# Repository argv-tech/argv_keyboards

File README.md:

# ARGV Keyboards

Keyboard Layout Editor definitions and printable keycap models for building and experimenting with custom keyboards.

The repository contains two keyboard layouts plus four ScottoCaps profiles. Ready-to-print meshes, editable CAD files, and original Shapr3D sources are included where available.

## Quick start

Choose a layout:

- [`keyboard-layout.json`](keyboard-layout.json) — split 80-key layout.
- [`keyboard-layout-no-split.json`](keyboard-layout-no-split.json) — non-split 106-key layout.

Then:

1. To view or edit the layout, open [Keyboard Layout Editor](https://www.keyboard-layout-editor.com/), select **Raw data**, and paste in the contents of the JSON file.
2. Choose a keycap profile and confirm that it supports your switch type and printing process.
3. Open a `.3mf` or `.stl` file in your slicer. Use the matching `.step` or `.shapr` file if you need to modify the geometry.
4. Print a single `1.00u` keycap first and test the stem fit before printing a full set.

## Keycap profiles

| Profile | Switches | Process | Contents | Documentation |
| --- | --- | --- | --- | --- |
| Flat | Cherry MX | FDM | Low-profile blanks and legends | [Printing notes](ScottoCaps/Flat/Readme.md) |
| Glass | Cherry MX and Choc | MSLA resin | Low-profile blanks from 1.00u to 10.00u, depending on switch type | [Safety and printing notes](ScottoCaps/Glass/README.md) |
| Scooped | Cherry MX and Choc | FDM | Concave, convex, homing, and multi-size caps; extensive legend collection | [Dimensions and printing notes](ScottoCaps/Scooped/Readme.md) |
| Sculpted | Cherry MX | FDM | R1–R5 blank keycaps in multiple sizes | [Dimensions and printing notes](ScottoCaps/Sculpted/Readme.md) |

### File formats

| Extension | Use |
| --- | --- |
| `.3mf` | Preferred slicer-ready model, including legend objects where applicable |
| `.stl` | Widely supported printable mesh |
| `.step` | Editable solid model for CAD applications |
| `.shapr` | Original Shapr3D project |
| `.json` | Keyboard Layout Editor raw data |

## Printing notes

- **Check compatibility first.** MX and Choc stems are different; use the directory for your switch type.
- **Test the stem fit.** The FDM stems use an approximately 0.15 mm tolerance, so the result depends on printer calibration and material. Never force a tight cap onto a switch.
- **Use dual extrusion for legends.** The Scooped legend variants are designed for a dual-extruder or multi-material printer.
- **Use biocompatible resin for Glass caps.** These caps are handled continuously and must be printed with an appropriate biocompatible resin. Read the [Glass safety notes](ScottoCaps/Glass/README.md) before printing.
- **Expect to tune the model or slicer.** Stem fit, rotation, and surface finish vary between printers. Each profile's documentation contains its recommended orientation and adjustments.

## Repository structure

```text
.
├── keyboard-layout.json
├── keyboard-layout-no-split.json
└── ScottoCaps/
    ├── Flat/
    │   ├── Blanks/
    │   └── Legends/
    ├── Glass/
    │   ├── Choc/
    │   └── MX/
    ├── Scooped/
    │   ├── Choc/
    │   └── MX/
    └── Sculpted/
        └── Blanks/
```

File names encode the key width in keyboard units (`u`). Scooped Choc models also include their physical footprint (`16x16`, `18x17`, or `18x18`), while Sculpted files include the row (`R1`–`R5`).

## Contributing

When adding or changing an asset:

- Keep the existing profile, switch, size, and variant naming conventions.
- Include an editable `.step` model alongside printable meshes when possible.
- Update the relevant profile README with any new dimensions, materials, or slicer requirements.
- Confirm that edited layout files still load in Keyboard Layout Editor.

## Credits

Special thanks to [ScottoKeebs](https://scottokeebs.com/) for the keycap models and printing guidance. The original designs and source files are available in the [ScottoKeebs GitHub repository](https://github.com/joe-scotto/scottokeebs/).

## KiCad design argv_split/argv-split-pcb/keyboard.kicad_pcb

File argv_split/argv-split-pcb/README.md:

# Split keyboard — one fabrication file, two cable-connected halves

Open `keyboard.kicad_pro` in KiCad 10. The PCB is one fabrication file containing two separately cuttable halves, so both halves can be sent in one order. U1 is the left Pico and U2 is the right Pico. Existing switch positions are preserved. Use standard, non-wireless Raspberry Pi Pico 1 modules with two 20-pin, 2.54 mm headers/sockets. USB connectors face the top edge. The modules supply their own regulation and USB circuitry.

All routed copper segments are 0.4 mm. The top and left edges were moved to leave at least 5 mm between the board edge and the switch courtyard; the other edges already meet that margin. The two halves have no PCB copper link: the four-wire cable is the only connection between them.

The project rules use a JLCPCB-friendly 2-layer baseline: 0.2 mm copper clearance, 0.4 mm minimum track width, 0.6/0.3 mm vias, 0.15 mm minimum via annular width, 0.09 mm soldermask expansion clearance, and 1.0 mm / 0.15 mm silkscreen text height and stroke. The 0.2 mm clearance is deliberately stricter than JLCPCB's published 0.10 mm capability so the board has process margin. See [JLCPCB's PCB capabilities](https://jlcpcb.com/capabilities/pcb-capabilities). Run the final DRC and JLCDFM check on the exported Gerbers before ordering.

The widened 0.4 mm tracks are applied to the existing compact routing. With the stricter 0.2 mm clearance rule, the current DRC report flags 75 clearance violations. Treat this revision as a routing review checkpoint and do not order until those routes are respaced or the JLCPCB DFM result confirms the actual geometry.

**Connector fit is not yet confirmed.** J1/J2 are standard 1×4, 2.54 mm through-hole headers for wiring to a separate connector PCB. They are not a verified footprint for the purchased four-pin part. Confirm its model, pitch, pin order, mounting, and cable continuity before fabrication. The board outlines are proposed outlines; check them against the intended plate/case.

## Four-wire interconnect

Use 3.3 V logic, full-duplex UART. GP0 is TX and GP1 is RX on both Picos. The right connector swaps the signal assignments, so a pin-for-pin cable crosses TX to RX:

| Cable pin | J1 / left | J2 / right |
| --- | --- | --- |
| 1 | U1 pin 39, VSYS | U2 pin 39, VSYS |
| 2 | Ground | Ground |
| 3 | U1 pin 1, GP0 / TX | U2 pin 2, GP1 / RX |
| 4 | U1 pin 2, GP1 / RX | U2 pin 1, GP0 / TX |

Cable connections: 1–1, 2–2, 3–3, 4–4. Do not add a second TX/RX crossover in the cable. Connect USB to one Pico; its onboard VBUS-to-VSYS Schottky diode supplies both halves through the VSYS wire. Do not connect the Pico 3V3 regulator outputs together. The schematic uses separate left/right net names because the cable is external, not a copper trace between boards.

Connect or disconnect the interconnect with USB power removed, especially if the purchased connector is TRRS: its contacts can short during insertion. This interface is not designed for live insertion.

## Matrix mapping

Diode cathodes connect to rows: firmware diode direction is `COL2ROW`. Each half has a logical 5×8 matrix with unused positions. GPIO names below refer to RP2040 GPIO numbers, not physical Pico pin numbers.

| GPIO | Pico pin | Left net | Right net |
| --- | --- | --- | --- |
| GP2 | 4 | ROW0 | ROW8 |
| GP3 | 5 | ROW1 | ROW7 |
| GP4 | 6 | ROW2 | ROW6 |
| GP5 | 7 | ROW3 | ROW5 |
| GP6 | 9 | ROW9 | ROW4 |
| GP7 | 10 | COL0 | COL8 |
| GP8 | 11 | COL1 | COL9 |
| GP9 | 12 | COL2 | COL10 |
| GP10 | 14 | COL3 | COL11 |
| GP11 | 15 | COL4 | COL12 |
| GP12 | 16 | COL5 | COL13 |
| GP13 | 17 | COL6 | COL14 |
| GP14 | 19 | COL7 | COL15 |

For split firmware, the global schematic ROW/COL numbers need translating to each half's local five rows and eight columns using this table. Firmware is not included or tested in this hardware project.

## Cable transport

Only the Pico-to-connector traces are on the PCBs. The inter-half TX/RX connection runs through the cable, and the cable can be rewired when a board is used on the opposite side. The right-hand connector swaps pins 3 and 4 so a straight pin-for-pin cable works with the two halves.

The UART baud rate is programmable; start at a conservative rate and verify the actual cable and firmware before increasing it. Scan rate, debounce and USB scheduling also affect keyboard latency.

QMK supports RP2040 full-duplex serial transport. Follow its driver configuration for GP0/GP1 and the selected driver; a complete keymap and handedness configuration are still required.

Sources: [RP2040 datasheet, UART §4.2 and I²C §4.3](https://datasheets.raspberrypi.com/rp2040/rp2040-datasheet.pdf), [QMK serial drivers](https://docs.qmk.fm/drivers/serial), [QMK RP2040 support](https://docs.qmk.fm/platformdev_rp2040), [Pico board datasheet](https://datasheets.raspberrypi.com/pico/pico-datasheet.pdf).

## Verification and previews

- `reports/erc.json`: schematic electrical checks.
- `reports/drc.json`: PCB design rules, unconnected items, and schematic parity.
- `reports/pcb-preview.png`: latest saved PCB preview.
- `reports/schematic/keyboard.svg`: schematic preview.
- `scripts/validate_design.py`: independent checks of connector and matrix pin mapping, and trace confinement to the two outlines.

If an already-open PCB editor shows long traces across the gap or below the boards, close that older in-memory view without saving and reopen the current project from disk. Avoid overwriting the updated file with the older view.

The scripts used for one-time construction are retained for traceability. Do not rerun `add_controllers.py`, `finish_connections.py`, `sync_board.py`, `finish_presentation.py`, or `clarify_schematic.py` on the finished design: some are one-time migrations and `sync_board.py` intentionally removes routing before autorouting. Edit the KiCad files normally for subsequent changes.

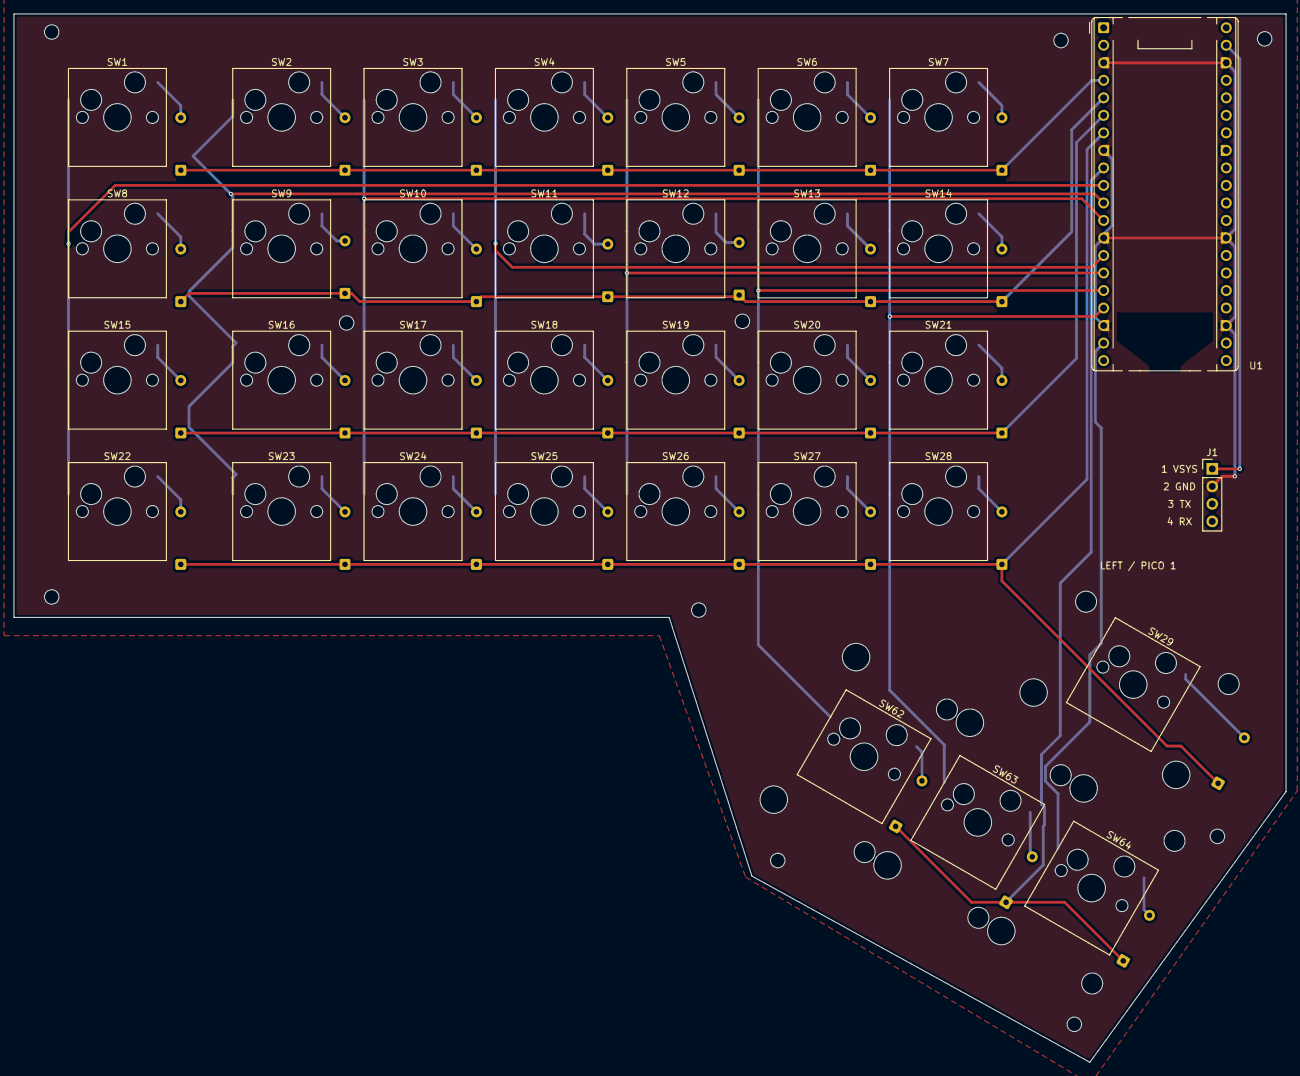
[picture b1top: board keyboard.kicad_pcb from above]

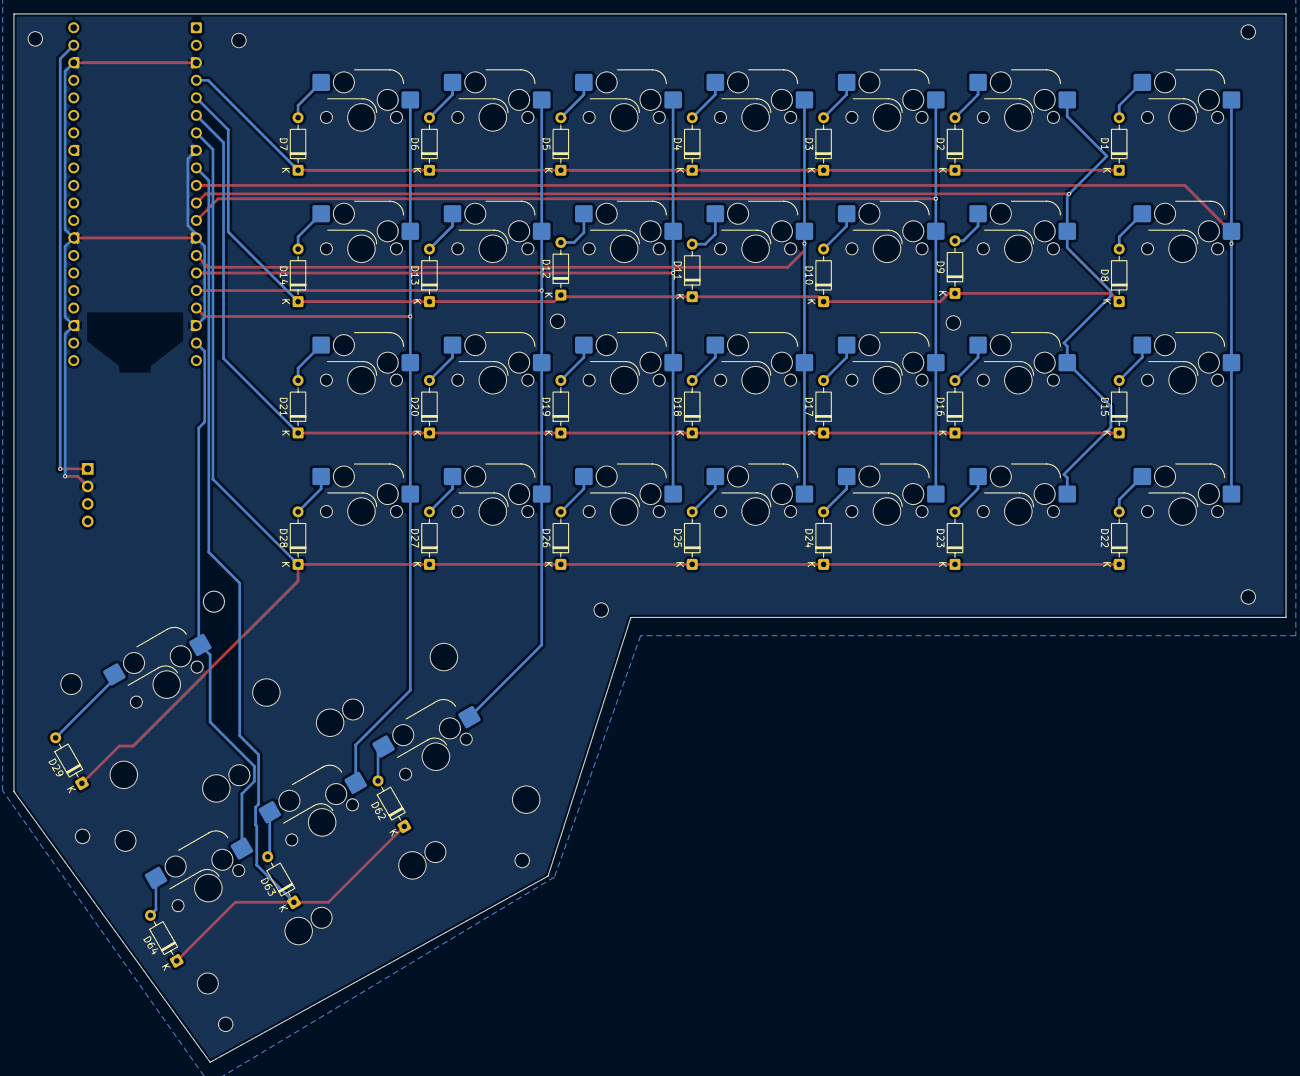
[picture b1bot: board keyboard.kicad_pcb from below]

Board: 2 copper layers, 184.4 x 152.0 mm, 80 parts (32 on the bottom side), 49 nets.

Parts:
D1, D2, D3, D4, D5, D6, D7, D8, D9, D10, D11, D12, D13, D14, D15, D16, D17, D18, D19, D20, D21, D22, D23, D24, D25, D26, D27, D28, D29, D62, D63, D64: D; D_DO-35_SOD27_P7.62mm_Horizontal
H1, H2, H3, H4, H5, H6, H7, H7#2, H7#3, H8: MountingHole_2.1mm
J1: BREAKOUT_4PIN; PinHeader_1x04_P2.54mm_Vertical
ST29, ST62, ST63, ST64: SW_stab; Stabilizer_Cherry_MX_2.00u
SW1, SW8, SW15, SW22: SW_Push; SW_Hotswap_Kailh_MX_1.50u
SW2, SW3, SW4, SW5, SW6, SW7, SW9, SW10, SW11, SW12, SW13, SW14, SW16, SW17, SW18, SW19, SW20, SW21, SW23, SW24, SW25, SW26, SW27, SW28, SW62, SW63, SW64: SW_Push; SW_Hotswap_Kailh_MX_1.00u
SW29: SW_Push; SW_Hotswap_Kailh_MX_2.00u
U1: RaspberryPi_Pico; RaspberryPi_Pico_Case_THT

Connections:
COL0: SW1.1, SW8.1, SW15.1, SW22.1, U1.10 (GPIO7)
COL1: SW2.1, SW9.1, SW16.1, SW23.1, U1.11 (GPIO8)
COL2: SW3.1, SW10.1, SW17.1, SW24.1, U1.12 (GPIO9)
COL3: SW4.1, SW11.1, SW18.1, SW25.1, U1.14 (GPIO10)
COL4: SW5.1, SW12.1, SW19.1, SW26.1, U1.15 (GPIO11)
COL5: SW6.1, SW13.1, SW20.1, SW27.1, SW62.1, U1.16 (GPIO12)
COL6: SW7.1, SW14.1, SW21.1, SW28.1, SW63.1, U1.17 (GPIO13)
COL7: SW29.1, SW64.1, U1.19 (GPIO14)
L_GND: J1.2, U1.3 (GND), U1.8 (GND), U1.13 (GND), U1.18 (GND), U1.23 (GND), U1.28 (GND), U1.38 (GND)
L_RX: J1.4, U1.2 (GPIO1)
L_TX: J1.3, U1.1 (GPIO0)
L_VSYS: J1.1, U1.39 (VSYS)
unnamed: D1.2 (A), SW1.2
unnamed: D2.2 (A), SW2.2
unnamed: D3.2 (A), SW3.2
unnamed: D4.2 (A), SW4.2
unnamed: D5.2 (A), SW5.2
unnamed: D6.2 (A), SW6.2
unnamed: D7.2 (A), SW7.2
unnamed: D8.2 (A), SW8.2
unnamed: D9.2 (A), SW9.2
unnamed: D10.2 (A), SW10.2
unnamed: D11.2 (A), SW11.2
unnamed: D12.2 (A), SW12.2
unnamed: D13.2 (A), SW13.2
unnamed: D14.2 (A), SW14.2
unnamed: D15.2 (A), SW15.2
unnamed: D16.2 (A), SW16.2
unnamed: D17.2 (A), SW17.2
unnamed: D18.2 (A), SW18.2
unnamed: D19.2 (A), SW19.2
unnamed: D20.2 (A), SW20.2
unnamed: D21.2 (A), SW21.2
unnamed: D22.2 (A), SW22.2
unnamed: D23.2 (A), SW23.2
unnamed: D24.2 (A), SW24.2
unnamed: D25.2 (A), SW25.2
unnamed: D26.2 (A), SW26.2
unnamed: D27.2 (A), SW27.2
unnamed: D28.2 (A), SW28.2
unnamed: D29.2 (A), SW29.2
unnamed: D62.2 (A), SW62.2
unnamed: D63.2 (A), SW63.2
unnamed: D64.2 (A), SW64.2
ROW0: D1.1 (K), D2.1 (K), D3.1 (K), D4.1 (K), D5.1 (K), D6.1 (K), D7.1 (K), U1.4 (GPIO2)
ROW1: D8.1 (K), D9.1 (K), D10.1 (K), D11.1 (K), D12.1 (K), D13.1 (K), D14.1 (K), U1.5 (GPIO3)
ROW2: D15.1 (K), D16.1 (K), D17.1 (K), D18.1 (K), D19.1 (K), D20.1 (K), D21.1 (K), U1.6 (GPIO4)
ROW3: D22.1 (K), D23.1 (K), D24.1 (K), D25.1 (K), D26.1 (K), D27.1 (K), D28.1 (K), D29.1 (K), U1.7 (GPIO5)
ROW9: D62.1 (K), D63.1 (K), D64.1 (K), U1.9 (GPIO6)

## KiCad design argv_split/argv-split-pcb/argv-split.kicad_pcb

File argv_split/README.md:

# argv_split

`argv_split` is a custom split ergonomic keyboard based on the ErgoDox. It keeps
the familiar two-half layout and thumb clusters while adapting the electronics
and key arrangement for this project.

## Features

- Split ergonomic layout with separated left and right key groups
- 76 keys with dedicated thumb clusters
- Kailh hot-swap sockets for MX-compatible switches
- One diode per key for matrix isolation
- A Raspberry Pi Pico controller on each half
- Four-pin connectors for communication and power between the halves

## Project files

The design files are located in this directory:

- [`argv_split_kicad/argv_split_kicad.kicad_sch`](argv_split_kicad/argv_split_kicad.kicad_sch) — circuit schematic
- [`argv_split_kicad/argv_split_kicad.kicad_pcb`](argv_split_kicad/argv_split_kicad.kicad_pcb) — PCB layout
- [`argv_split_kicad/argv_split_kicad.kicad_pro`](argv_split_kicad/argv_split_kicad.kicad_pro) — KiCad project settings
- [`keyboard-layout.json`](keyboard-layout.json) — physical layout data for Keyboard Layout Editor
- [`keyboard_layout.dxf`](keyboard_layout.dxf) — exported layout geometry

Open `argv_split_kicad/argv_split_kicad.kicad_pro` in KiCad to inspect or
modify the design.

## Layout

The keyboard uses a 76-key split layout:

- 12 function keys (`F1`–`F12`), with six on each half
- 56 keys in four horizontal main rows, with seven keys per half in each row
- 8 thumb keys in two clusters rotated 30 degrees toward the center

The outer keys in the main block are 1.5u wide. The inner columns contain
parenthesis, brace, bracket, and quote keys. The left thumb cluster contains a
2u `Space` key above three 2u-tall keys labeled `Crtl`, `Linux`, and `Alt`. The
right cluster mirrors it with a 2u `backspace` key above `Return`, `Linux`, and
`Crtl`. These names and spellings match the current layout data.

To view or edit the layout, open Keyboard Layout Editor, choose **Raw data**, and
paste in the contents of [`keyboard-layout.json`](keyboard-layout.json). The
labels in this file describe the intended physical layout; the active key
behavior still depends on the keyboard firmware and keymap.

## Status

This is a custom hardware project and may still be a work in progress. Review
the schematic, PCB layout, footprints, clearances, and connector pinout before
ordering boards or assembling the keyboard.

## Attribution

This design is inspired by and derived from the ErgoDox keyboard layout, with
modifications made for the ARGV split keyboard project.

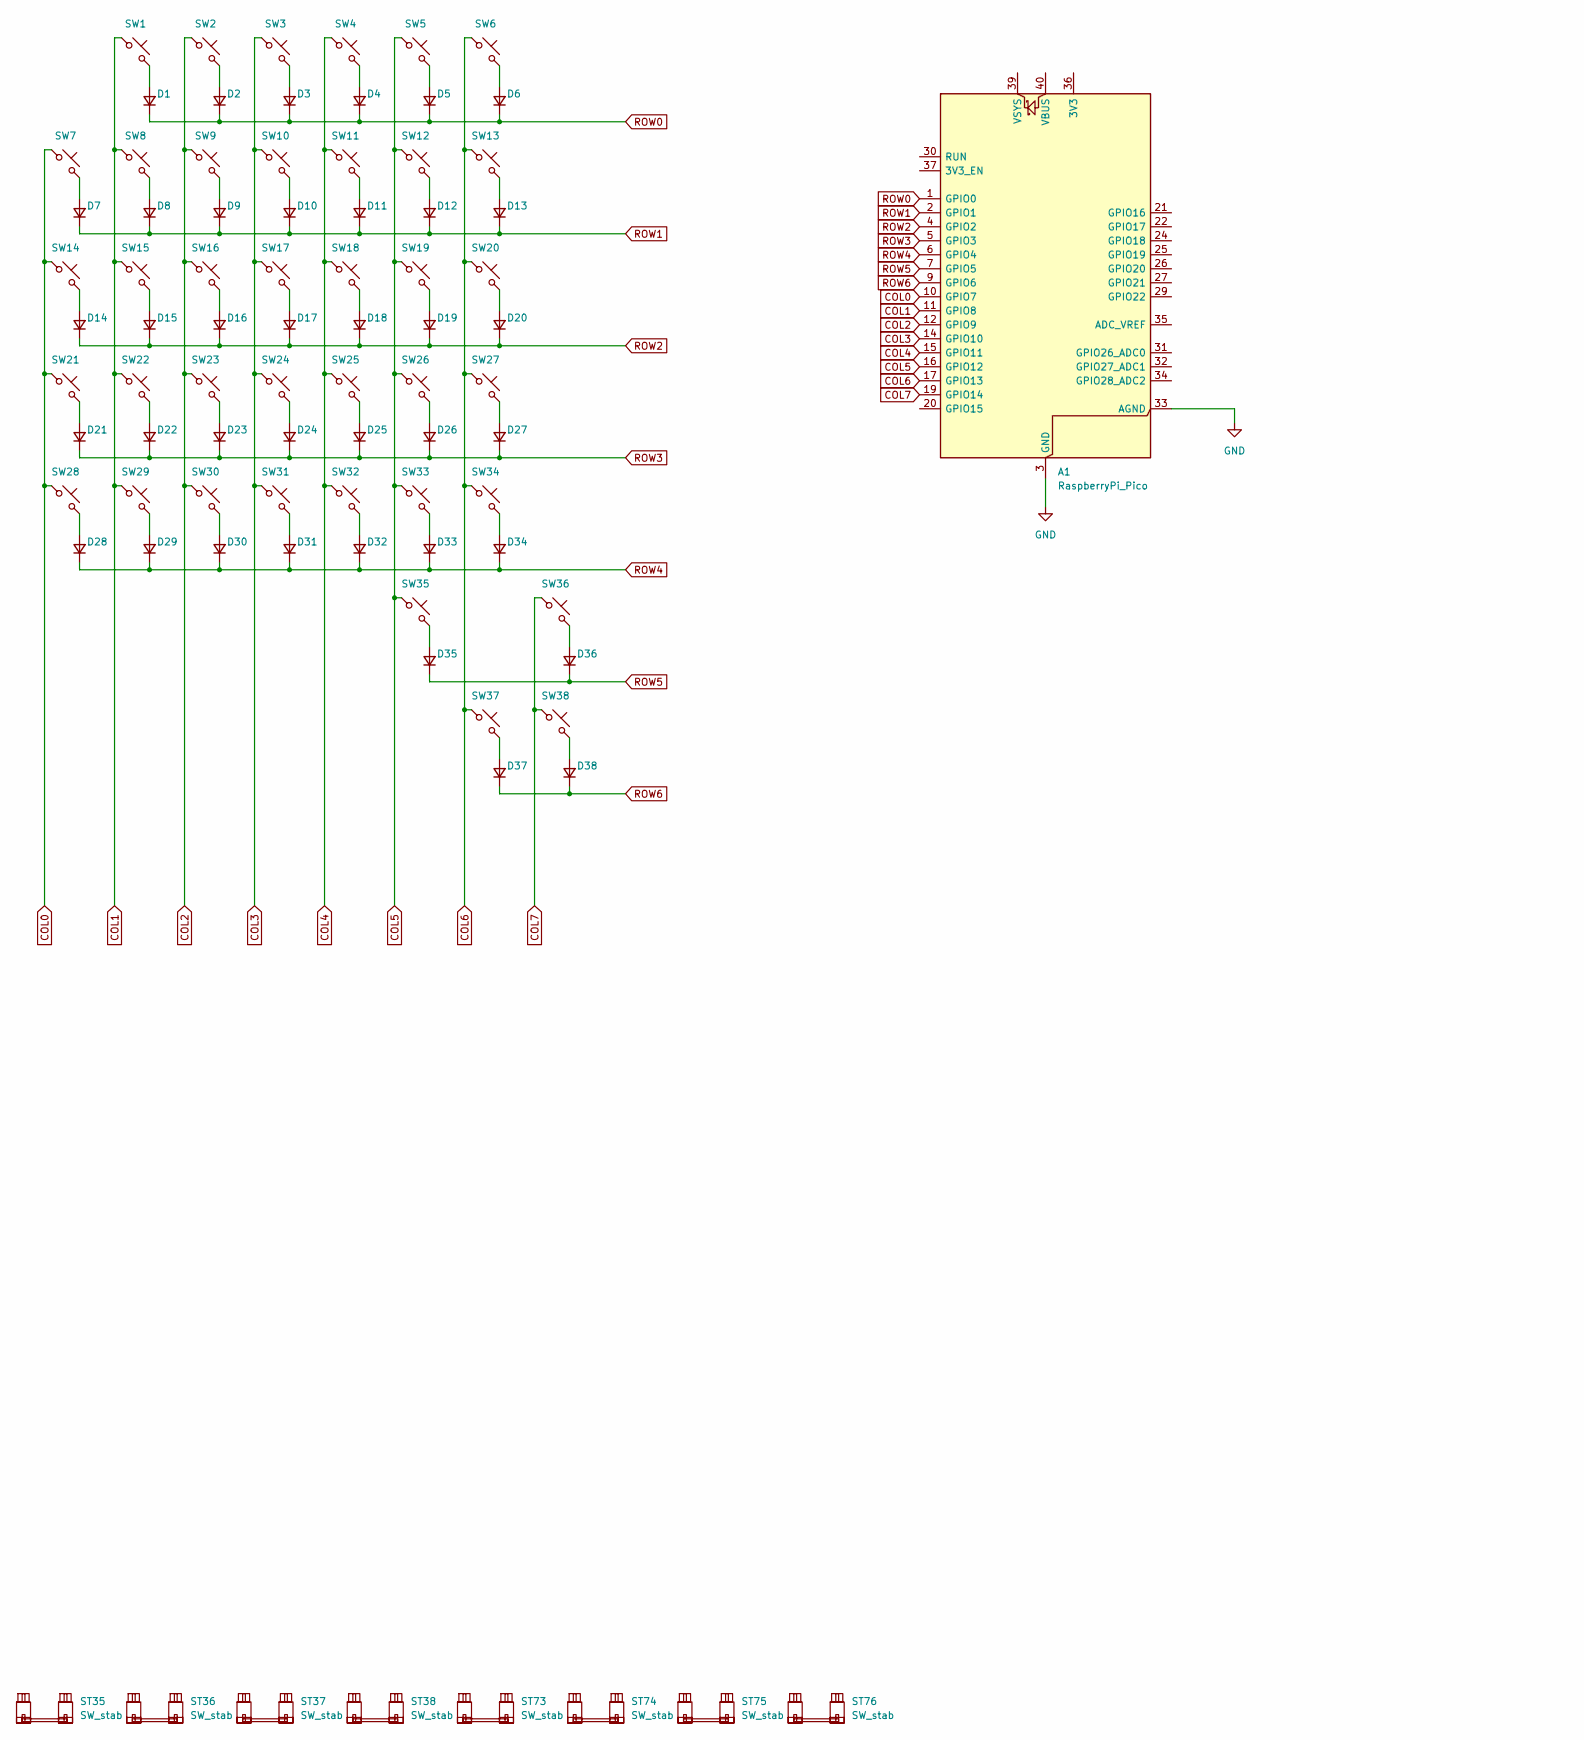
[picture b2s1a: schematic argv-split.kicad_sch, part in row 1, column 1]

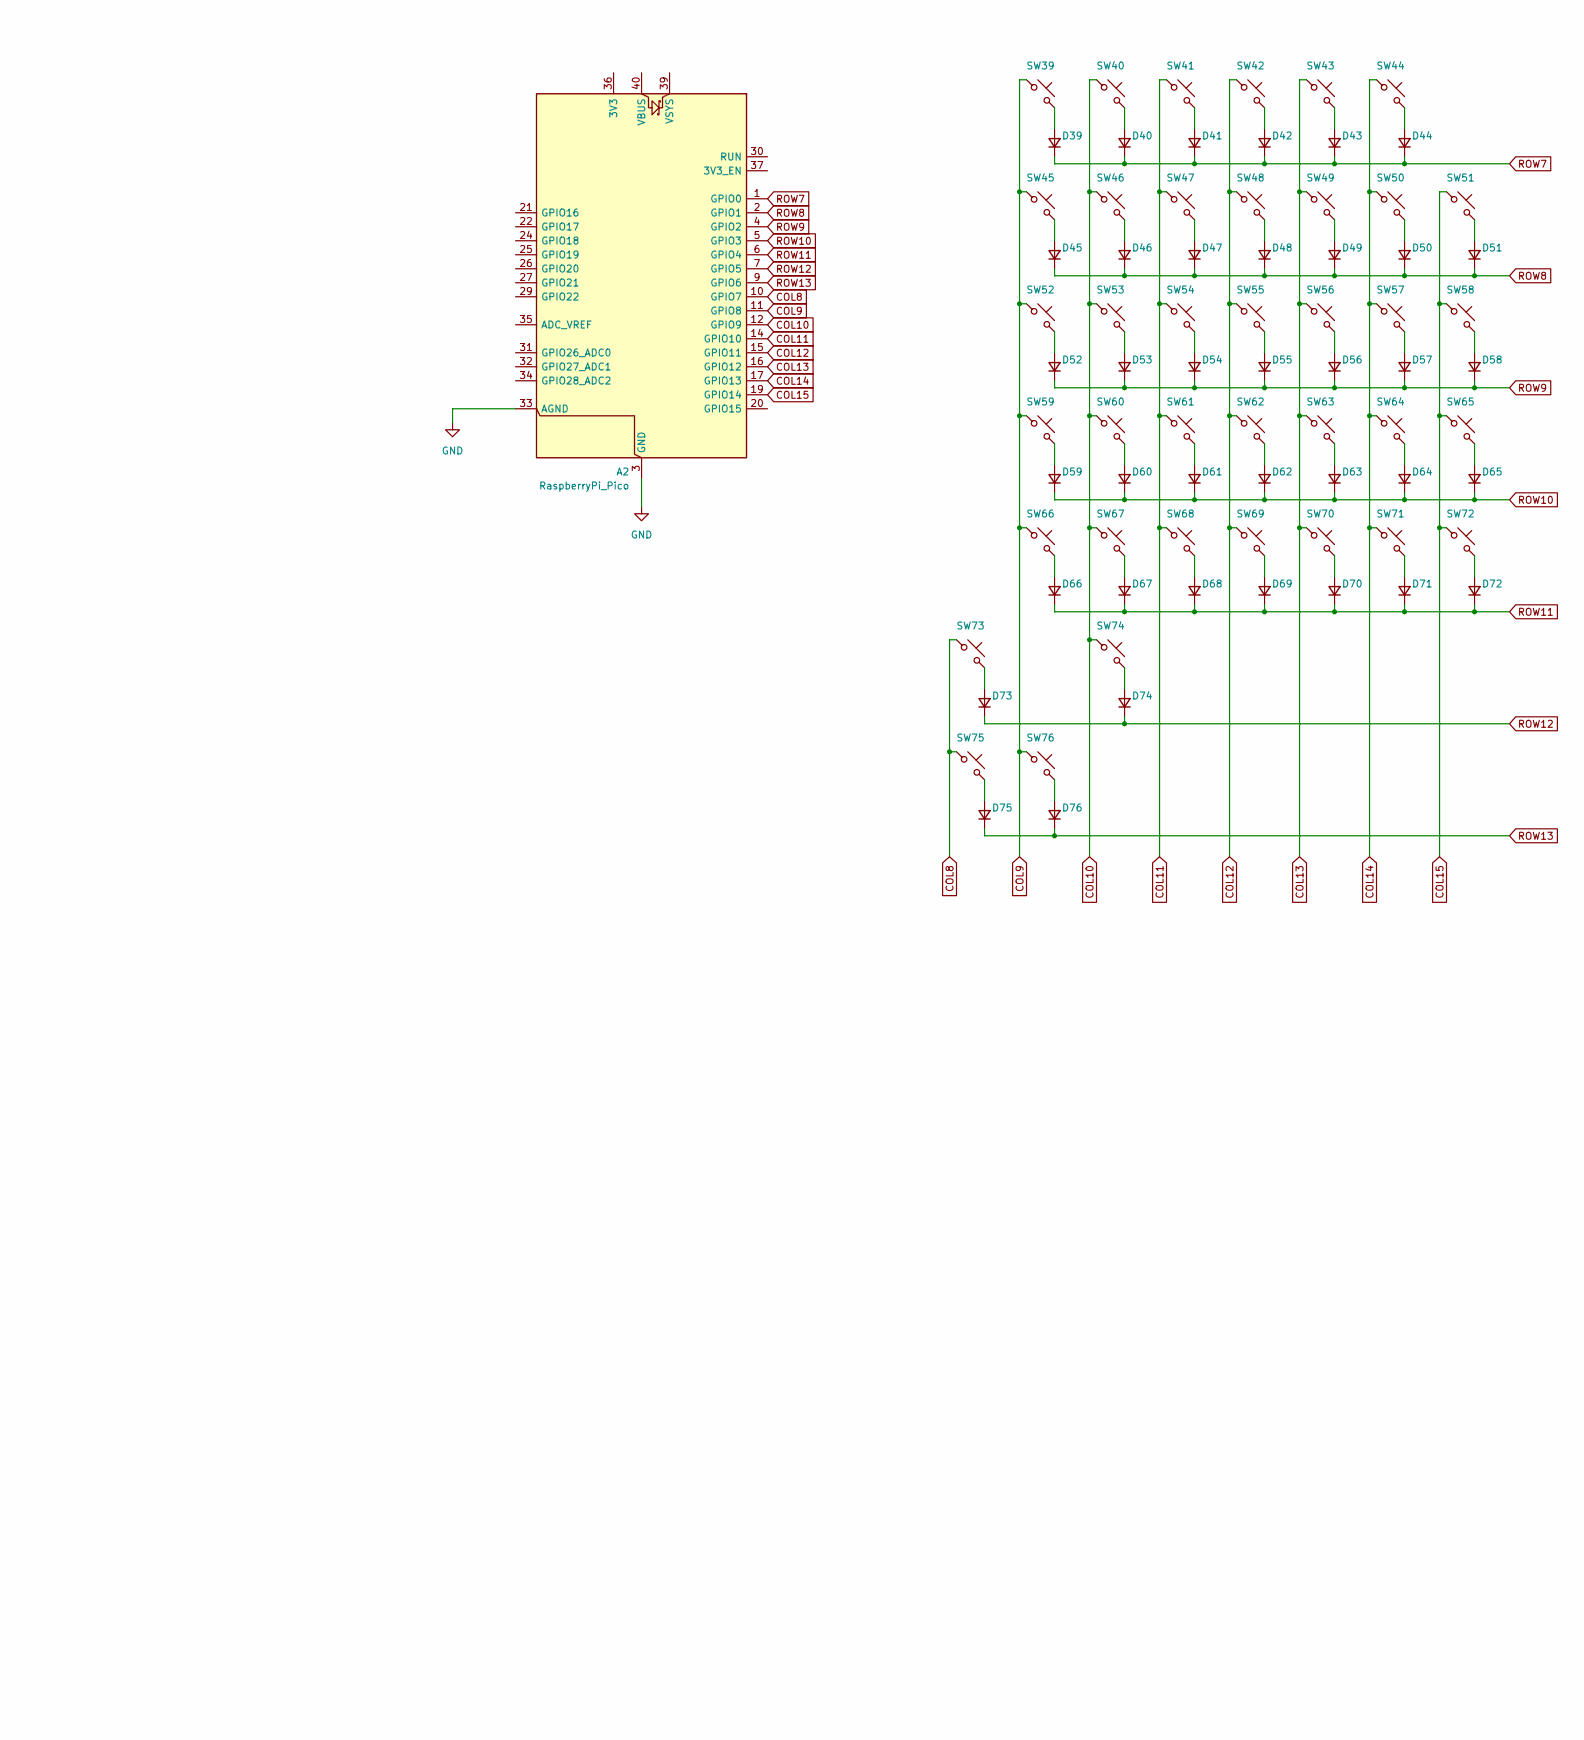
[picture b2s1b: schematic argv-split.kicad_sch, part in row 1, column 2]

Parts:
A1, A2: RaspberryPi_Pico; RaspberryPi_Pico_Common_Unspecified
D1, D2, D3, D4, D5, D6, D7, D8, D9, D10, D11, D12, D13, D14, D15, D16, D17, D18, D19, D20, D21, D22, D23, D24, D25, D26, D27, D28, D29, D30, D31, D32, D33, D34, D35, D36, D37, D38, D39, D40, D41, D42, D43, D44, D45, D46, D47, D48, D49, D50, D51, D52, D53, D54, D55, D56, D57, D58, D59, D60, D61, D62, D63, D64, D65, D66, D67, D68, D69, D70, D71, D72, D73, D74, D75, D76: D; D_DO-35_SOD27_P7.62mm_Horizontal
ST35, ST36, ST37, ST38, ST73, ST74, ST75, ST76: SW_stab; Stabilizer_Cherry_MX_2.00u
SW1, SW2, SW3, SW4, SW5, SW6, SW8, SW9, SW10, SW11, SW12, SW13, SW15, SW16, SW17, SW18, SW19, SW20, SW22, SW23, SW24, SW25, SW26, SW27, SW29, SW30, SW31, SW32, SW33, SW34, SW35, SW37, SW38, SW39, SW40, SW41, SW42, SW43, SW44, SW45, SW46, SW47, SW48, SW49, SW50, SW52, SW53, SW54, SW55, SW56, SW57, SW59, SW60, SW61, SW62, SW63, SW64, SW66, SW67, SW68, SW69, SW70, SW71, SW74, SW75, SW76: SW_Push; SW_Hotswap_Kailh_MX_1.00u
SW7, SW14, SW21, SW28, SW51, SW58, SW65, SW72: SW_Push; SW_Hotswap_Kailh_MX_1.50u
SW36, SW73: SW_Push; SW_Hotswap_Kailh_MX_2.00u

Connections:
COL0: A1.10 (GPIO7), SW7.1, SW14.1, SW21.1, SW28.1
COL1: A1.11 (GPIO8), SW1.1, SW8.1, SW15.1, SW22.1, SW29.1
COL2: A1.12 (GPIO9), SW2.1, SW9.1, SW16.1, SW23.1, SW30.1
COL3: A1.14 (GPIO10), SW3.1, SW10.1, SW17.1, SW24.1, SW31.1
COL4: A1.15 (GPIO11), SW4.1, SW11.1, SW18.1, SW25.1, SW32.1
COL5: A1.16 (GPIO12), SW5.1, SW12.1, SW19.1, SW26.1, SW33.1, SW35.1
COL6: A1.17 (GPIO13), SW6.1, SW13.1, SW20.1, SW27.1, SW34.1, SW37.1
COL7: A1.19 (GPIO14), SW36.1, SW38.1
COL8: A2.10 (GPIO7), SW73.1, SW75.1
COL9: A2.11 (GPIO8), SW39.1, SW45.1, SW52.1, SW59.1, SW66.1, SW76.1
COL10: A2.12 (GPIO9), SW40.1, SW46.1, SW53.1, SW60.1, SW67.1, SW74.1
COL11: A2.14 (GPIO10), SW41.1, SW47.1, SW54.1, SW61.1, SW68.1
COL12: A2.15 (GPIO11), SW42.1, SW48.1, SW55.1, SW62.1, SW69.1
COL13: A2.16 (GPIO12), SW43.1, SW49.1, SW56.1, SW63.1, SW70.1
COL14: A2.17 (GPIO13), SW44.1, SW50.1, SW57.1, SW64.1, SW71.1
COL15: A2.19 (GPIO14), SW51.1, SW58.1, SW65.1, SW72.1
GND: A1.3 (GND), A1.8 (GND), A1.13 (GND), A1.18 (GND), A1.23 (GND), A1.28 (GND), A1.33 (AGND), A1.38 (GND), A2.3 (GND), A2.8 (GND), A2.13 (GND), A2.18 (GND), A2.23 (GND), A2.28 (GND), A2.33 (AGND), A2.38 (GND)
unnamed: D1.2 (A), SW1.2
unnamed: D2.2 (A), SW2.2
unnamed: D3.2 (A), SW3.2
unnamed: D4.2 (A), SW4.2
unnamed: D5.2 (A), SW5.2
unnamed: D6.2 (A), SW6.2
unnamed: D7.2 (A), SW7.2
unnamed: D8.2 (A), SW8.2
unnamed: D9.2 (A), SW9.2
unnamed: D10.2 (A), SW10.2
unnamed: D11.2 (A), SW11.2
unnamed: D12.2 (A), SW12.2
unnamed: D13.2 (A), SW13.2
unnamed: D14.2 (A), SW14.2
unnamed: D15.2 (A), SW15.2
unnamed: D16.2 (A), SW16.2
unnamed: D17.2 (A), SW17.2
unnamed: D18.2 (A), SW18.2
unnamed: D19.2 (A), SW19.2
unnamed: D20.2 (A), SW20.2
unnamed: D21.2 (A), SW21.2
unnamed: D22.2 (A), SW22.2
unnamed: D23.2 (A), SW23.2
unnamed: D24.2 (A), SW24.2
unnamed: D25.2 (A), SW25.2
unnamed: D26.2 (A), SW26.2
unnamed: D27.2 (A), SW27.2
unnamed: D28.2 (A), SW28.2
unnamed: D29.2 (A), SW29.2
unnamed: D30.2 (A), SW30.2
unnamed: D31.2 (A), SW31.2
unnamed: D32.2 (A), SW32.2
unnamed: D33.2 (A), SW33.2
unnamed: D34.2 (A), SW34.2
unnamed: D35.2 (A), SW35.2
unnamed: D36.2 (A), SW36.2
unnamed: D37.2 (A), SW37.2
unnamed: D38.2 (A), SW38.2
unnamed: D39.2 (A), SW39.2
unnamed: D40.2 (A), SW40.2
unnamed: D41.2 (A), SW41.2
unnamed: D42.2 (A), SW42.2
unnamed: D43.2 (A), SW43.2
unnamed: D44.2 (A), SW44.2
unnamed: D45.2 (A), SW45.2
unnamed: D46.2 (A), SW46.2
unnamed: D47.2 (A), SW47.2
unnamed: D48.2 (A), SW48.2
unnamed: D49.2 (A), SW49.2
unnamed: D50.2 (A), SW50.2
unnamed: D51.2 (A), SW51.2
unnamed: D52.2 (A), SW52.2
unnamed: D53.2 (A), SW53.2
unnamed: D54.2 (A), SW54.2
unnamed: D55.2 (A), SW55.2
unnamed: D56.2 (A), SW56.2
unnamed: D57.2 (A), SW57.2
unnamed: D58.2 (A), SW58.2
unnamed: D59.2 (A), SW59.2
unnamed: D60.2 (A), SW60.2
unnamed: D61.2 (A), SW61.2
unnamed: D62.2 (A), SW62.2
unnamed: D63.2 (A), SW63.2
unnamed: D64.2 (A), SW64.2
unnamed: D65.2 (A), SW65.2
unnamed: D66.2 (A), SW66.2
unnamed: D67.2 (A), SW67.2
unnamed: D68.2 (A), SW68.2
unnamed: D69.2 (A), SW69.2
unnamed: D70.2 (A), SW70.2
unnamed: D71.2 (A), SW71.2
unnamed: D72.2 (A), SW72.2
unnamed: D73.2 (A), SW73.2
unnamed: D74.2 (A), SW74.2
unnamed: D75.2 (A), SW75.2
unnamed: D76.2 (A), SW76.2
ROW0: A1.1 (GPIO0), D1.1 (K), D2.1 (K), D3.1 (K), D4.1 (K), D5.1 (K), D6.1 (K)
ROW1: A1.2 (GPIO1), D7.1 (K), D8.1 (K), D9.1 (K), D10.1 (K), D11.1 (K), D12.1 (K), D13.1 (K)
ROW2: A1.4 (GPIO2), D14.1 (K), D15.1 (K), D16.1 (K), D17.1 (K), D18.1 (K), D19.1 (K), D20.1 (K)
ROW3: A1.5 (GPIO3), D21.1 (K), D22.1 (K), D23.1 (K), D24.1 (K), D25.1 (K), D26.1 (K), D27.1 (K)
ROW4: A1.6 (GPIO4), D28.1 (K), D29.1 (K), D30.1 (K), D31.1 (K), D32.1 (K), D33.1 (K), D34.1 (K)
ROW5: A1.7 (GPIO5), D35.1 (K), D36.1 (K)
ROW6: A1.9 (GPIO6), D37.1 (K), D38.1 (K)
ROW7: A2.1 (GPIO0), D39.1 (K), D40.1 (K), D41.1 (K), D42.1 (K), D43.1 (K), D44.1 (K)
ROW8: A2.2 (GPIO1), D45.1 (K), D46.1 (K), D47.1 (K), D48.1 (K), D49.1 (K), D50.1 (K), D51.1 (K)
ROW9: A2.4 (GPIO2), D52.1 (K), D53.1 (K), D54.1 (K), D55.1 (K), D56.1 (K), D57.1 (K), D58.1 (K)
ROW10: A2.5 (GPIO3), D59.1 (K), D60.1 (K), D61.1 (K), D62.1 (K), D63.1 (K), D64.1 (K), D65.1 (K)
ROW11: A2.6 (GPIO4), D66.1 (K), D67.1 (K), D68.1 (K), D69.1 (K), D70.1 (K), D71.1 (K), D72.1 (K)
ROW12: A2.7 (GPIO5), D73.1 (K), D74.1 (K)
ROW13: A2.9 (GPIO6), D75.1 (K), D76.1 (K)

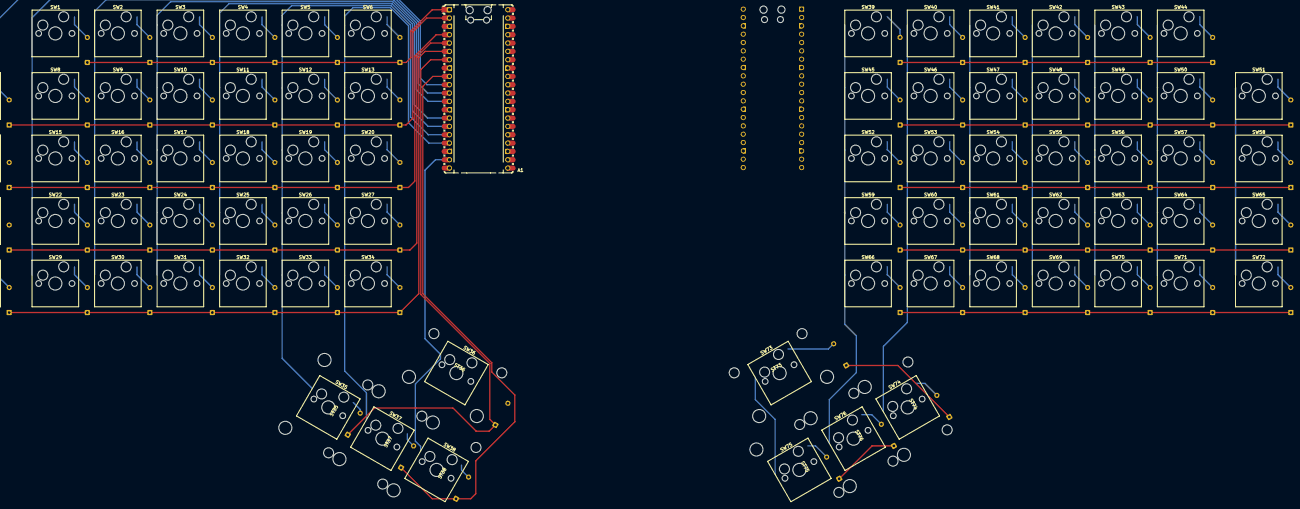
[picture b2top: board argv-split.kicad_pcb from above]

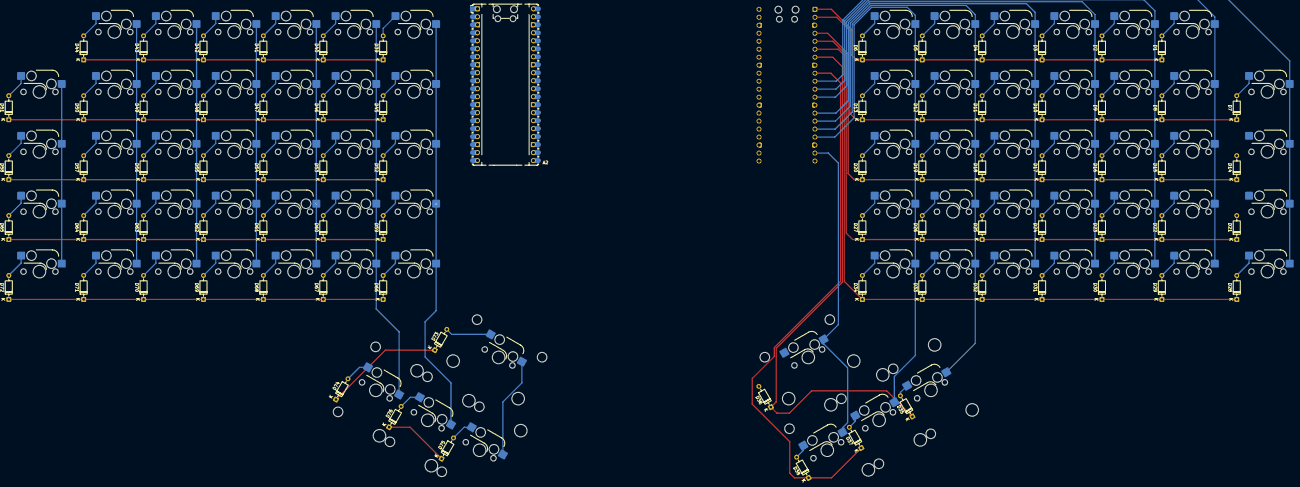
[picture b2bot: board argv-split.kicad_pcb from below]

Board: 2 copper layers, 162 parts (77 on the bottom side), 107 nets.
